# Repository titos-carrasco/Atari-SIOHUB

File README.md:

# Atari-SIOHUB
Hub/Splitter para conexión SIO de Atari

* Puntas del conector: AT60-202-2031, alternativa en aliexpress 0460-202-20141
* Los símbolos de atari tomados desde https://github.com/pmandes/atari-sio-connector

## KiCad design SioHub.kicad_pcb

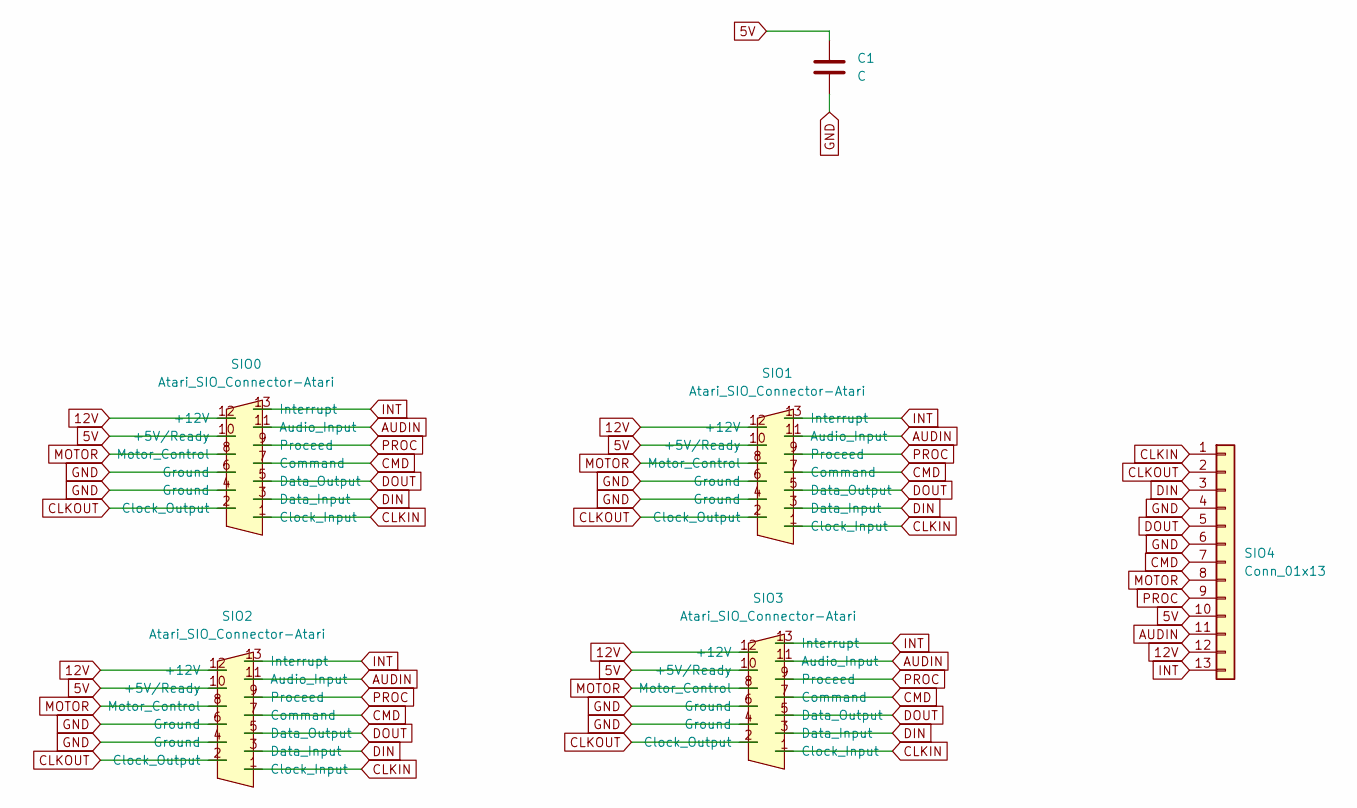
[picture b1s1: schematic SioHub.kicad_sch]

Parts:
C1: C; C_Disc_D3.8mm_W2.6mm_P2.50mm
SIO0, SIO1, SIO2, SIO3: Atari_SIO_Connector-Atari; Atari_SIO_Socket
SIO4: Conn_01x13; PinHeader_1x13_P2.54mm_Vertical

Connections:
5V: C1.1, SIO0.10 (+5V/Ready), SIO1.10 (+5V/Ready), SIO2.10 (+5V/Ready), SIO3.10 (+5V/Ready), SIO4.10
12V: SIO0.12 (+12V), SIO1.12 (+12V), SIO2.12 (+12V), SIO3.12 (+12V), SIO4.12
AUDIN: SIO0.11 (Audio_Input), SIO1.11 (Audio_Input), SIO2.11 (Audio_Input), SIO3.11 (Audio_Input), SIO4.11
CLKIN: SIO0.1 (Clock_Input), SIO1.1 (Clock_Input), SIO2.1 (Clock_Input), SIO3.1 (Clock_Input), SIO4.1
CLKOUT: SIO0.2 (Clock_Output), SIO1.2 (Clock_Output), SIO2.2 (Clock_Output), SIO3.2 (Clock_Output), SIO4.2
CMD: SIO0.7 (Command), SIO1.7 (Command), SIO2.7 (Command), SIO3.7 (Command), SIO4.7
DIN: SIO0.3 (Data_Input), SIO1.3 (Data_Input), SIO2.3 (Data_Input), SIO3.3 (Data_Input), SIO4.3
DOUT: SIO0.5 (Data_Output), SIO1.5 (Data_Output), SIO2.5 (Data_Output), SIO3.5 (Data_Output), SIO4.5
GND: C1.2, SIO0.4 (Ground), SIO0.6 (Ground), SIO1.4 (Ground), SIO1.6 (Ground), SIO2.4 (Ground), SIO2.6 (Ground), SIO3.4 (Ground), SIO3.6 (Ground), SIO4.4, SIO4.6
INT: SIO0.13 (Interrupt), SIO1.13 (Interrupt), SIO2.13 (Interrupt), SIO3.13 (Interrupt), SIO4.13
MOTOR: SIO0.8 (Motor_Control), SIO1.8 (Motor_Control), SIO2.8 (Motor_Control), SIO3.8 (Motor_Control), SIO4.8
PROC: SIO0.9 (Proceed), SIO1.9 (Proceed), SIO2.9 (Proceed), SIO3.9 (Proceed), SIO4.9

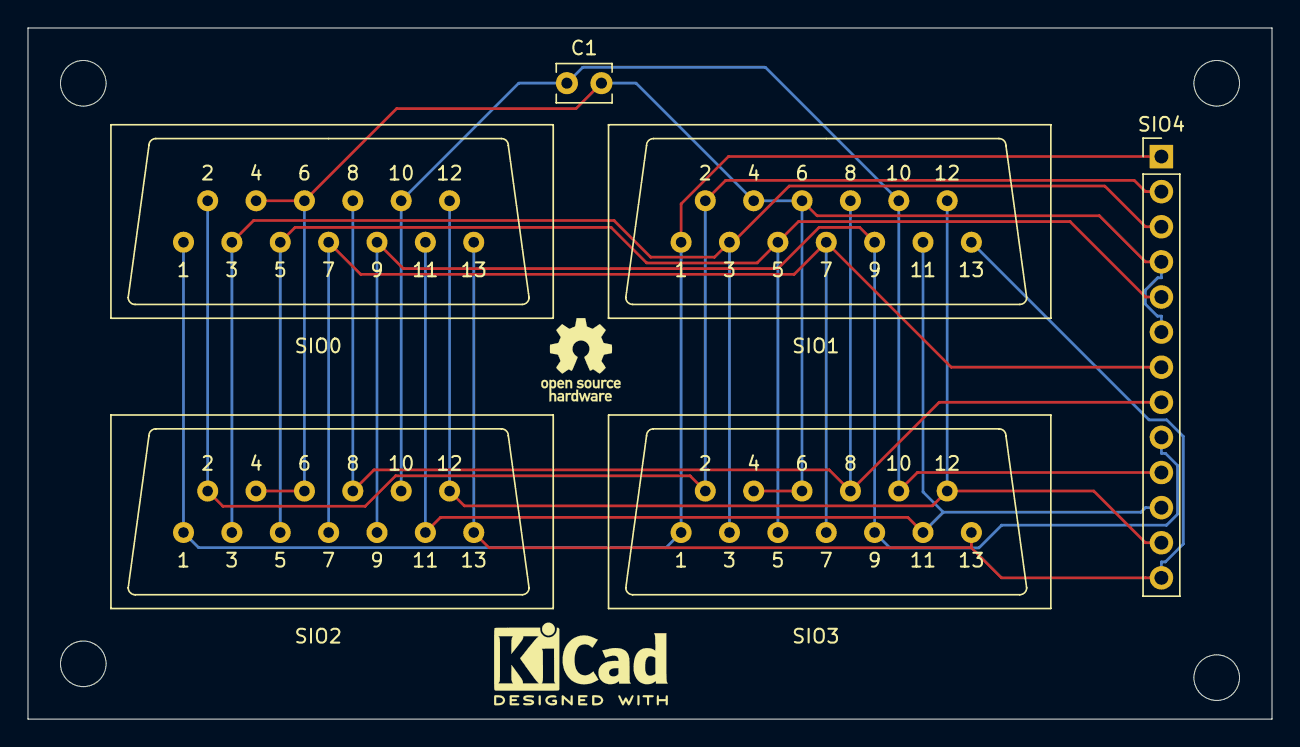
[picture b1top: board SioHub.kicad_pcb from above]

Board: 2 copper layers, 90.0 x 50.0 mm, 8 parts (0 on the bottom side), 12 nets.

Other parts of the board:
DesignedWithKiCad: KiCad-Logo2_5mm_SilkScreen
OSHW: OSHW-Logo_5.7x6mm_SilkScreen

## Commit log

2024-06-19 Primera versión publicada
